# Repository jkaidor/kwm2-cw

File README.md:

# kwm2-cw
CW support in the Collins KWM-2 was not good.  In order to transmit code, they used an audio oscillator inputting into the SSB transmit chain.  To make this work, they used a high injection frequency - in my radio, 1750Hz.  So the user hears 1750 Hz as the sidetone, and also must listen to their QSO partner at 1750 Hz.  Very high and squeaky.  A comfortable 600hz would have landed its second harmonic inside the bandpass of the mechanical filter.
My card fixes this by translating the 1750Hz ( either sidetone or other signal, doesn't matter ) to 650Hz.  It does so by first bandpass filtering the 1750Hz.  Then mixing it down to 650Hz with an 1100Hz oscillator.  Then a high pass filter to chop off the unwanted image frequency.  The card does this all in *software*.  It has a PJRC Teensy 4.1 processor card, and I used the PJRC audio library to implement it.
This depository includes the KiCAD files, the gerbers, and the Arduino sketch.
The card mounts to the back of the KWM-2 PTO.  There's a couple of convenient studs sticking out of it.
In my implementation, I built a power supply mounted on a tube plug, plugged into the noise blanker socket.
I also made room for a BHI noise reduction module.  So now, when I set my KWM-2 to noise blanker mode, I get DSP noise reduction.  Actual noise blankers don't do much nowadays;  The Woodpecker is long gone, and I don't operate mobile with my boatanchors.
The CW fixer also supports two bandwidths - wide and narrow.  When you select CW from the mode switch, you get one of those bandwidths.  Select it again, and you get the other one.
There is an unused lug on the mode switch that gives a ground in CW mode - very convenient!

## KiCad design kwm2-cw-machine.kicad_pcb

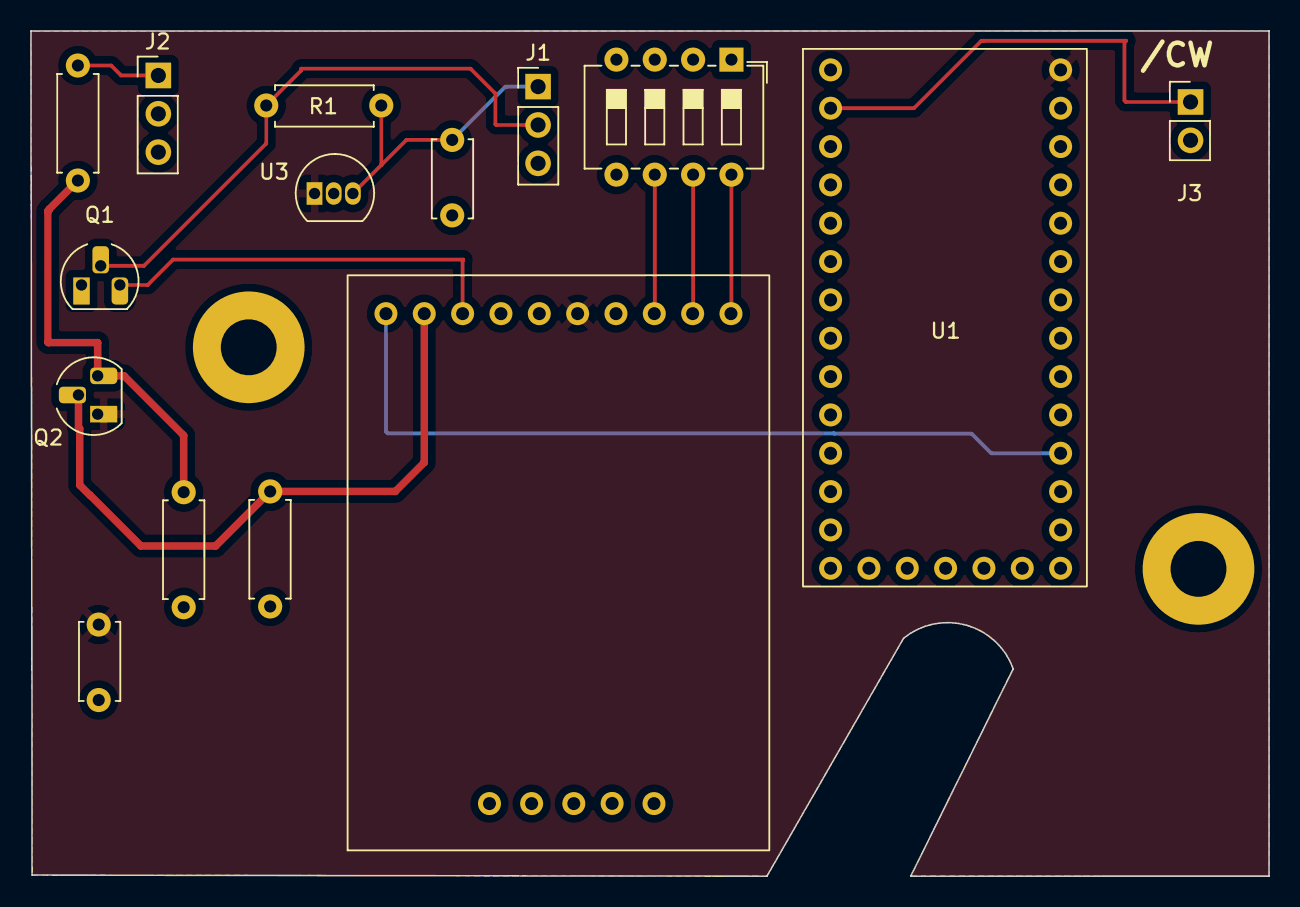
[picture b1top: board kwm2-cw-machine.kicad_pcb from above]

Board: 2 copper layers, 82.0 x 56.0 mm, 15 parts (0 on the bottom side), 13 nets.

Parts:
C1, C2: C; C_Disc_D5.0mm_W2.5mm_P5.00mm
J1: To NB Socket; PinHeader_1x03_P2.54mm_Vertical
J2: To Audio; PinHeader_1x03_P2.54mm_Vertical
J3: Conn_01x02_Pin; PinHeader_1x02_P2.54mm_Vertical
Q1: 2N3904; TO-92_HandSolder
Q2: Q_NJFET_DSG; TO-92_HandSolder
R1, R2, R3, R4: R_US; R_Axial_DIN0207_L6.3mm_D2.5mm_P7.62mm_Horizontal
SW1: SW_DIP_x04; SW_DIP_SPSTx04_Slide_6.7x11.72mm_W7.62mm_P2.54mm_LowProfile
U1: Teensy4.0; Teensy 4.0
U2: BHI 1901-PCB
U3: L78L05; TO-92_Inline

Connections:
+5V: C1.1, Q2.1 (D), U1.33 (VIN), U2.5 (V+), U3.1 (VO)
+9V: C2.1, J1.1, R1.1, U3.3 (VI)
GND: C1.2, C2.2, J1.3, J2.2, J3.2, Q1.1 (E), R2.2, R4.2, SW1.1, SW1.2, SW1.3, U1.1 (GND), U1.17 (GND), U1.32 (GND), U2.7 (GND), U3.2 (GND)
unnamed: J1.2, Q1.2 (B), R1.2
unnamed: J2.1, R3.1
unnamed: J3.1, U1.2 (0_RX1_CRX2_CS1)
unnamed: Q1.3 (C), U2.8 (Noise_Reduction_Off)
unnamed: Q2.3 (G), R2.1, R3.2
unnamed: Q2.2 (S), R4.1, U2.9 (Audio_In)
unnamed: U1.23 (16_A2_RX4_SCL1), U2.10 (Audio_Output)
unnamed: SW1.8, U2.1 (Reduction_Bit_0)
unnamed: SW1.7, U2.2 (Reduction_Bit_1)
unnamed: SW1.6, U2.3 (Reduction_bit_2)

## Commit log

2025-10-23 Add files via upload
    Initial files for the KWM-2 CW machine.
